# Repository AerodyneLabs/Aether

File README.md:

Aether
======

High-altitude balloon pico-tracker

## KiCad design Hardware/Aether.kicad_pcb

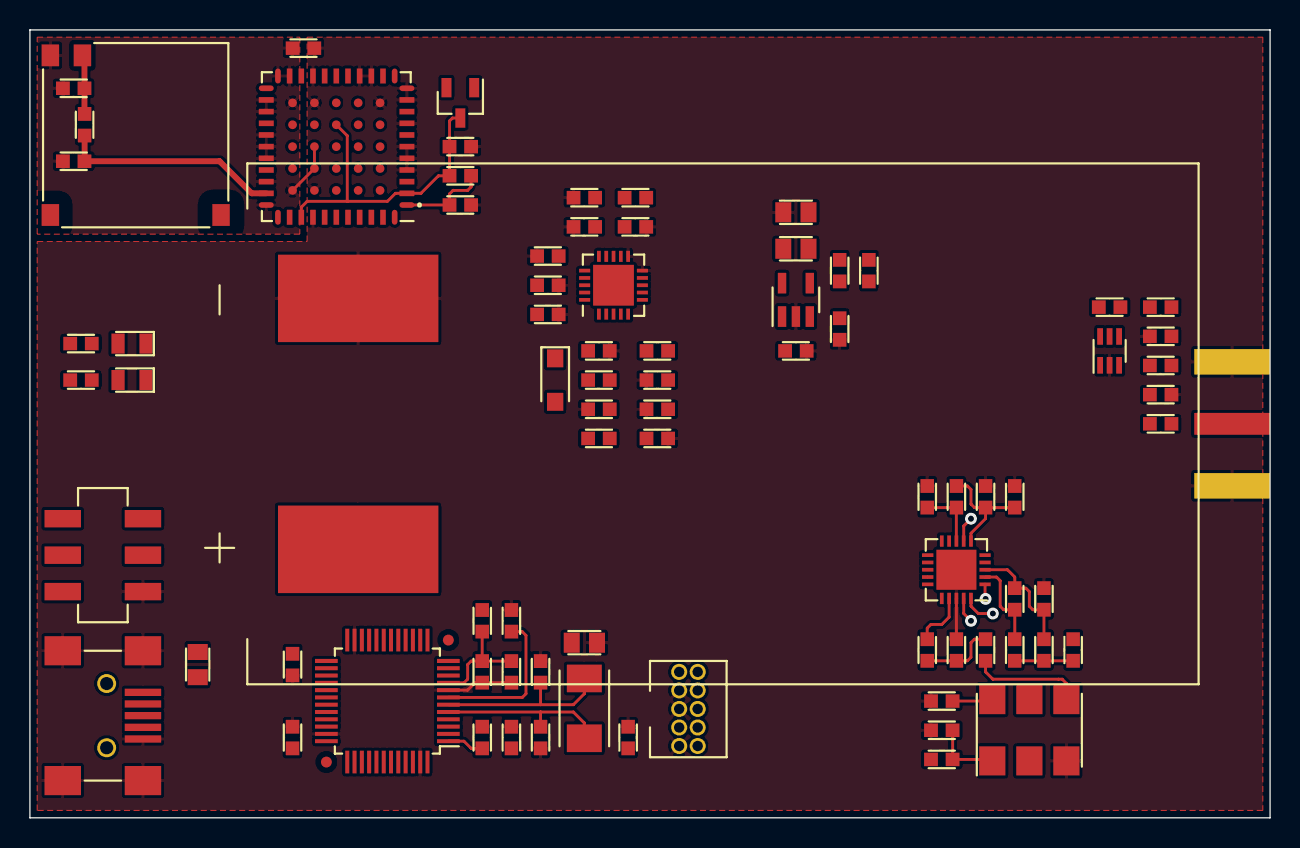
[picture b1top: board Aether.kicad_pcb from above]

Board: 2 copper layers, 85.0 x 54.0 mm, 82 parts (0 on the bottom side), 58 nets.

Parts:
AE1: Antenna-Balanced; Antenna_Proant-AB-430
B1: 3.7V; Batt_PL-703562-2C-Folded
C1, C2, C12, C15, C21: 1uF; CAPC1608N
C3: DNP; CAPC1608N
C4: 1.8pF; CAPC1608N
C5, C7, C9, C13, C16, C20, C22, C26: 0.1uF; CAPC1608N
C6, C8: 30pF; CAPC1608N
C10, C33: 10uF; CAPC2012N
C17, C18, C25, C27, C30: Capacitor; CAPC1608N
C19, C23: 470pF; CAPC1608N
C24, C28: 0.01uF; CAPC1608N
C29, C31, C34, C35: 4.7uF; CAPC1608N
C32: 18pF; CAPC1608N
D1, D2: LED; LEDC2012N
D3: MBR120ESFT1G; SODFL3616N
FB1, FB2: Ferrite; INDC1608N
J1: Conn_Cortex-JTAG-10; Conn_Samtec-FTSH-105-D-K
J2: Conn_USB-Mini; Conn_USB-Mini-690-005-299-043
J3: Conn_Coax; Conn_RF_Linx-CONSMA003.031-L
L1: 3.3nH; INDC1608N
L2, L3, L4, L5, L6: Inductor; INDC1608N
L7: 2.2uH; INDC2012N
PTC1: PTC; RESC2012N
Q1: BSS84; SOT95P240-3N-GSD
R1, R19: 36k; RESC1608N
R2: 0; RESC1608N
R3, R4, R17, R18: Resistor; RESC1608N
R5, R7, R8, R9, R10, R13, R14, R15, R20: 100k; RESC1608N
R6: 160; RESC1608N
R11: 270k; RESC1608N
R12: 453k; RESC1608N
R16: 2k; RESC1608N
RT1: 10k; RESC1608N
SW1: DPDT; SW_CK-JS202011SCQN
U1: Venus838LPx-L; Sensor_Venus838
U2: STM32L151CBT; QFP50P900X900-48N
U3: Si4464; QFN50P400X400-21T275X275N
U4: AS213; SOT65P220-6N
U5: NCP1521; SOT95P275-5L40N
U6: MCP73871; QFN50P400X400-21T280X280N
X1: 8MHz; Crystal_Abracon-ABM3
X3: 27MHz; Osc_CTS-357

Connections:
+3V3: C5.1, C7.1, C9.1, C10.1, C20.1, C21.1, C26.1, C32.1, C33.1, FB1.1, FB2.1, J1.1, L7.2, Q1.S, R3.1, R4.1, R12.1, U1.18, U2.24, U2.36, U2.48, U3.6, X3.6
+5VP: C30.1, C31.1, D3.C, PTC1.2, R11.1, U6.3, U6.4, U6.9, U6.18, U6.19
+BATT: C29.1, C35.1, SW1.3, U5.1, U6.1, U6.20
/GPS/GND_RF: AE1.2, C3.2, C4.2, R2.1, U1.21, U1.22, U1.24, U1.25, U1.27, U1.28, U1.29, U1.31, U1.33, U1.61, U1.62, U1.65, U1.69
/GPS/GPS1: C3.1, L1.1, U1.32
/GPS/GPS2: AE1.1, C4.1, L1.2
/GPS/GPS_RX: U1.42, U2.21
/GPS/GPS_TX: U1.44, U2.22
/Microcontroller/BOOT: R5.1, U2.44
/Microcontroller/BSense: R19.2, R20.1
/Microcontroller/OSC_I: C6.1, U2.5, X1.1
/Microcontroller/OSC_O: C8.1, U2.6, X1.2
/Microcontroller/SSense: R9.2, R10.1
/Microcontroller/SWCLK: J1.4, U2.37
/Microcontroller/SWDIO: J1.2, U2.34
/Microcontroller/USB_DM: J2.2, U2.32
/Microcontroller/USB_DP: J2.3, U2.33
/Microcontroller/VCO_EN: U2.13, X3.2
/Microcontroller/VCO_MOD: R6.1, U2.14
/Microcontroller/VDDA: C12.1, C13.1, FB1.2, U2.9
/Microcontroller/VLCD: C15.1, U2.1
/Microcontroller/XCVR_SCLK: U2.39, U3.12
/Microcontroller/XCVR_SDI: U2.41, U3.14
/Microcontroller/XCVR_SDO: U2.40, U3.13
/Microcontroller/~RST: C16.1, J1.10, U2.7
/Microcontroller/~XCVR_CS: U2.38, U3.15
/Power/PWR: SW1.2, U5.3
/Radio/LO: C28.2, U3.17
/Radio/RX: C19.2, U4.3
/Radio/RX_En: U3.19, U4.4
/Radio/RXn: C17.1, L2.2, L3.1, U3.3
/Radio/RXp: C18.1, L2.1, U3.2
/Radio/TX_En: U3.20, U4.6
/Radio/VDDA: C22.1, FB2.2, U3.8
GND: B1.2, C1.2, C2.2, C5.2, C6.2, C7.2, C8.2, C9.2, C10.2, C12.2, C13.2, C15.2, C16.2, C17.2, C20.2, C21.2, C22.2, C24.2, C25.2, C26.2, C27.2, C29.2, C30.2, C31.2, C33.2, C34.2, C35.2, J1.3, J1.5, J1.9, J2.5, J2.S, J3.2, R2.2, R5.2, R8.2, R10.2, R13.2, R14.2, R15.2, R16.2, R18.2, R20.2, RT1.2, SW1.1, U1.4, U1.5, U1.6, U1.8, U1.10, U1.11, U1.14, U1.15, U1.19, U1.37, U1.49, U1.60, U1.64, U2.8, U2.23, U2.35, U2.47, U3.18, U3.21, U4.2, U5.2, U6.10, U6.11, U6.21, X3.3
unnamed: B1.1, C34.1, R19.1, U6.14, U6.15, U6.16
unnamed: C1.1, Q1.D, R1.1, U1.2, U1.36, U1.58
unnamed: C2.1, R1.2, U1.1
unnamed: C18.2, C19.1, L3.2
unnamed: C23.1, U4.5
unnamed: C23.2, L4.1
unnamed: C24.1, R6.2, X3.1
unnamed: C25.1, L4.2, L5.1
unnamed: C27.1, L5.2, L6.1
unnamed: C28.1, R7.2, R8.1
unnamed: C32.2, R12.2, R13.1, U5.4
unnamed: D1.A, R3.2
unnamed: D2.A, R4.2
unnamed: D3.A, R9.1
unnamed: J2.1, PTC1.1
unnamed: J3.1, L6.2
unnamed: L7.1, U5.5
unnamed: R7.1, X3.4
unnamed: R11.2, R14.1, U6.2
unnamed: R15.1, U6.12
unnamed: R16.1, U6.13
unnamed: R17.1, U6.5
unnamed: R17.2, R18.1, RT1.1

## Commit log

2014-01-30 Basic GPS and Transmitter schematic
2014-02-01 More schematic layout
    GPS mostly finished
    Additional transmitter layout
    Core added
2014-02-02 Finish modulation section
2014-02-02 Add GPS performance control
2014-02-03 Switch GPS power to main 3v3 bus
2014-02-03 Add core crystal
2014-02-03 Voltage regulator values
2014-02-03 GPS values
2014-02-03 Connectors
2014-02-03 Change to 28 pin MCU
2014-02-03 Modulation section values
2014-02-03 Annotation and netlist
2014-02-03 Rough footprint association
2014-02-04 Rough layout
2014-02-04 RF routing
2014-02-04 Something changed
2014-02-05 Add expansion headers
2014-02-05 Change to soft SPI, routing
2014-02-06 Additional layout
2014-02-06 Optimize some values
2014-02-07 Transmitter RF components
2014-02-08 Transmitter support components
2014-02-08 Voltage regulator components
2014-02-08 Microcontroller components
2014-02-08 Modulation components
2014-02-08 GPS components
2014-02-08 RF layout
2014-02-08 Board configuration
2014-02-08 Ground pour and rearrange expansion
2014-02-09 Majority of layout
2014-02-09 Add fiducials and mount holes
2014-02-09 Add RF ground pour
2014-02-09 Finish layout
2014-02-09 Prepare for fab
2014-02-09 Add gerber zip to ignore
2014-02-24 Consolidate LED resistors
    See #1
2014-02-24 Consolidate audio filter
    Consolidate pull up resistors and audio filter.
    Consolidate loop filter capacitor and audio filter.
    See #1
2014-02-24 Re-add fiducials
2014-02-25 Update audio filter
    See #1
2014-02-26 Something changed apparently
2014-03-06 Empty firmware
2014-03-07 Add basic DDS code
2014-03-10 Add UART configuration
    Redo formatting
2014-03-10 Skeleton UART ISRs
2014-03-10 Implement UART buffers
2014-03-11 Basic EEPROM emulation
2014-03-11 New gerbers
2014-03-14 Basic command parsing
2014-03-14 Move processing outside USCI RX ISR
    Add new rxChar global and SERIAL_RX status bit.
    Add new SERIAL_CR status bit to detect \r\n endings.
2014-03-14 Switch all \n to \r\n
2014-03-14 Process buffered rxPkt instead of rxBuf
2014-03-14 No longer need to exhaust buffer
2014-03-14 Implement configuration
2014-06-29 Prepare for r2
    Delete board, netlist, associations
    Clear annotations
2014-06-29 Prepare for new GPS
    Remove connections to subsheet
    Clear subsheet
2014-06-29 Add Venus datasheet
2014-06-29 Add W3011A antenna datasheet
2014-06-29 Add Venus commands datasheet
2014-06-29 Add Venus838 to schematic
2014-06-29 Connect GPS power
2014-06-29 Prepare for new core
    Clear core subsheet
    Remove expansion
2014-06-29 Remove old MSP430 code
2014-06-30 Add core pins
2014-07-29 Add STM32L100
2014-07-29 Add datasheet
2014-07-29 Core pin placeholders
2014-07-30 Add programming connector to core
2014-07-30 Add crystals and connect pins
2014-07-30 Remove old transmitter
2014-07-30 Add Si4463
2014-07-30 Rename: transmitter->transceiver
2014-07-31 RX signal chain topology
2014-07-31 Add power planning notes
2014-07-31 Add battery charger basic circuit
2014-08-02 Add LO
2014-08-02 System 3v3 regulator
2014-08-02 Add GPS load switch
2014-08-02 Transceiver power control pins
2014-08-03 Add buck converter datasheet
2014-08-14 Add gps enable connection
2014-08-15 Add LO control pins
2014-08-17 New development strategy
2014-08-17 GPS schematic and layout
2014-08-17 Radio schematic and rough layout
2014-08-17 Add application notes
2014-08-18 5v regulator schematic and rough layout
2014-08-19 3v3 regulator schematic and rough layout
2014-08-29 Add charger and batteries to schematic and board
2014-08-30 Core support circuitry
2014-08-30 Add usb
2014-08-30 Connect subsystems
2014-10-13 Blinky demo for STM32L152
2014-10-13 Sine wave generation
2014-10-15 Add .comarker and .cogui to gitignore
2014-10-15 Update to support sine amplitude and offset
2014-10-15 Move main.cpp to firmware directory
2014-10-15 Baud rate demonstration
2014-10-15 Refactor for readability
2014-10-15 Change symbol timer for TIM6
    Timers 6/7 are intended for DAC triggering
2014-10-15 Move DAC processing out of ISR
2014-10-15 Change all clocks to 32MHz
    For #21
2014-10-15 Fix wave generation with hard coded values
    Closes #21
    Closes #20
2014-10-16 UART send demo
2014-10-17 Add APRS specs
2014-10-17 Add RingBuffer class
2014-10-17 Refactor NVIC configuration for readability
2014-10-17 Add {} to empty while loops to comply with style guide
2014-10-17 Implement rx buffer
2014-10-18 Implement tx buffer
2014-10-18 Move source files into src folder
2014-10-18 RingBuffer doxygen
2014-10-18 Document RingBuffer implementation
2014-10-19 Add TinyGPS++ submodule
2014-10-19 Remove TingyGPSPlus
2014-10-19 Remove old library files from project
2014-10-20 Rough GPS parsing implementation
    Demo ignores altitude, printf appears to be broken with float types.
2014-10-23 APRS Packet class skeleton
2014-10-23 APRSPacket get/set skeleton
2014-10-25 Add AX25 specification
2014-10-29 Basic callsign encoding in APRSPacket
2014-11-07 Configuration program framework
2014-11-09 FirmwareTab placeholder UI/functions
2014-11-09 Rough profile management UI
2014-11-09 Add profile meta data management
2014-11-10 Rough profile conditions model
2014-11-10 Change profile conditions model/view to use combo boxes
2014-11-11 Rough tree model
2014-11-11 Fix conditions being copied to new profile
    Also fix some other random things with no side effects
2014-11-11 Implement creation of conditions/outputs
2014-12-17 Switch to new MCU datasheet
2014-12-19 Clear hardware for new version
2014-12-21 GPS circuitry
    For #29
2014-12-22 MCU core circuitry
    Closes #24
2014-12-22 USB circuitry
    Closes #27
2014-12-23 Rough TCVR circuitry
    First order TX topology #28
    Core circuitry for TCVR, closes #23
2014-12-23 Basic battery charger circuitry
    #26
2014-12-23 Charger circuitry values
    #26
2014-12-23 Add solar charging capability
2014-12-23 Add 3v3 regulator
2014-12-23 Add power switch
2014-12-26 Oscillator selection
    Closes #35
2014-12-26 GPS BoM fields
    #33
2014-12-26 Rough GPS layout
    #34 #31
2014-12-26 Add RF switch
2014-12-29 Update general layout
2014-12-29 Power sheet BOM fields
    Remove annotations
2014-12-29 BOM fields
2014-12-29 Netlist and association
    Closes #34
2014-12-29 Subsystem partioning
2014-12-29 MCU routing
2014-12-29 Small changes
2014-12-30 Remove old datasheets
2014-12-30 Pinmapping
2015-01-01 RF layout/routing
2015-01-01 Additional datasheets
